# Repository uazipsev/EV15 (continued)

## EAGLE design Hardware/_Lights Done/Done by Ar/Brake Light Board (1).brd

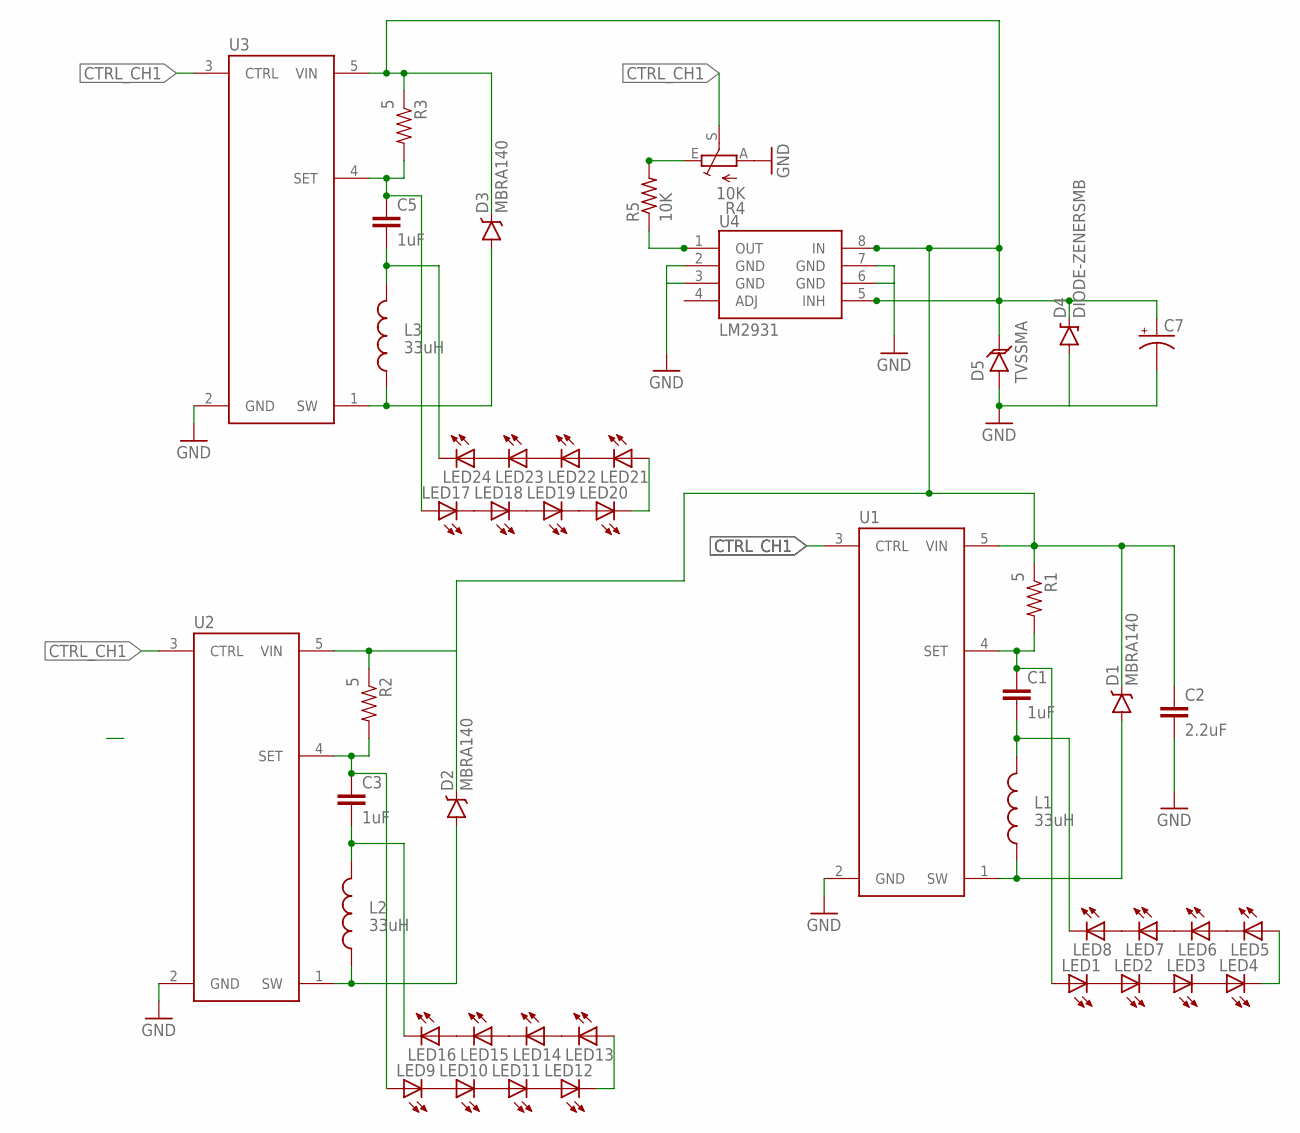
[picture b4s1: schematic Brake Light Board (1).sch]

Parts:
C1, C3, C5: 1uF; 1206
C2: 2.2uF; 1206
C7: CAP_POL6032; EIA6032
D1, D2, D3: MBRA140; SMA-DIODE
D4: DIODE-ZENERSMB; SMB-DIODE
D5: TVSSMA; SMA-DIODE
L1, L2, L3: 33uH; SRN6045
LED1, LED2, LED3, LED4, LED5, LED6, LED7, LED8, LED9, LED10, LED11, LED12, LED13, LED14, LED15, LED16, LED17, LED18, LED19, LED20, LED21, LED22, LED23, LED24: LED5MM
R1, R2, R3: 5; 0805
R4: 10K; B25P
R5: 10K; R0805
U1, U2, U3: AL8805; SOT23-5
U4: LM2931; SO08

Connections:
CTRL_CH1: R4.S, U1.3 (CTRL), U2.3 (CTRL), U3.3 (CTRL)
GND: C2.2, C7.P$2 (-), D4.A, D5.A, R4.A, U1.2 (GND), U2.2 (GND), U3.2 (GND), U4.2 (GND), U4.6 (GND), U4.7 (GND)
unnamed: LED1.K (C), LED2.A
unnamed: LED2.K (C), LED3.A
unnamed: LED3.K (C), LED4.A
unnamed: C1.2, L1.2, LED8.K (C)
unnamed: LED5.K (C), LED6.A
unnamed: LED6.K (C), LED7.A
unnamed: LED7.K (C), LED8.A
unnamed: LED9.K (C), LED10.A
unnamed: LED4.K (C), LED5.A
unnamed: LED10.K (C), LED11.A
unnamed: LED11.K (C), LED12.A
unnamed: C3.2, L2.2, LED16.K (C)
unnamed: LED13.K (C), LED14.A
unnamed: LED14.K (C), LED15.A
unnamed: LED15.K (C), LED16.A
unnamed: LED12.K (C), LED13.A
unnamed: LED17.K (C), LED18.A
unnamed: LED18.K (C), LED19.A
unnamed: LED19.K (C), LED20.A
unnamed: C5.2, L3.2, LED24.K (C)
unnamed: LED21.K (C), LED22.A
unnamed: LED22.K (C), LED23.A
unnamed: LED23.K (C), LED24.A
unnamed: LED20.K (C), LED21.A
unnamed: R4.E, R5.2
unnamed: R5.1, U4.1 (OUT)
OUT+: C1.1, LED1.A, R1.2, U1.4 (SET)
OUT+1: C3.1, LED9.A, R2.2, U2.4 (SET)
OUT+2: C5.1, LED17.A, R3.2, U3.4 (SET)
SW: D1.A, L1.1, U1.1 (SW)
SW1: D2.A, L2.1, U2.1 (SW)
SW2: D3.A, L3.1, U3.1 (SW)
VIN: C2.1, C7.P$1 (+), D1.C, D2.C, D3.C, D4.C, D5.C, R1.1, R2.1, R3.1, U1.5 (VIN), U2.5 (VIN), U3.5 (VIN), U4.5 (INH), U4.8 (IN)

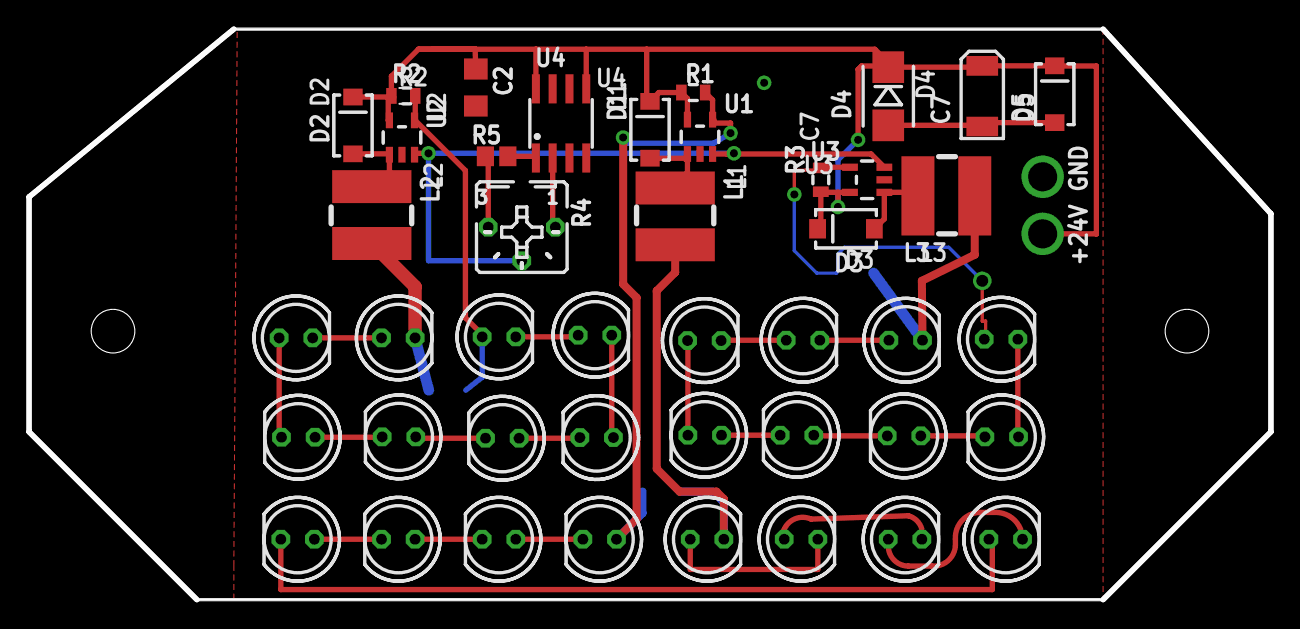
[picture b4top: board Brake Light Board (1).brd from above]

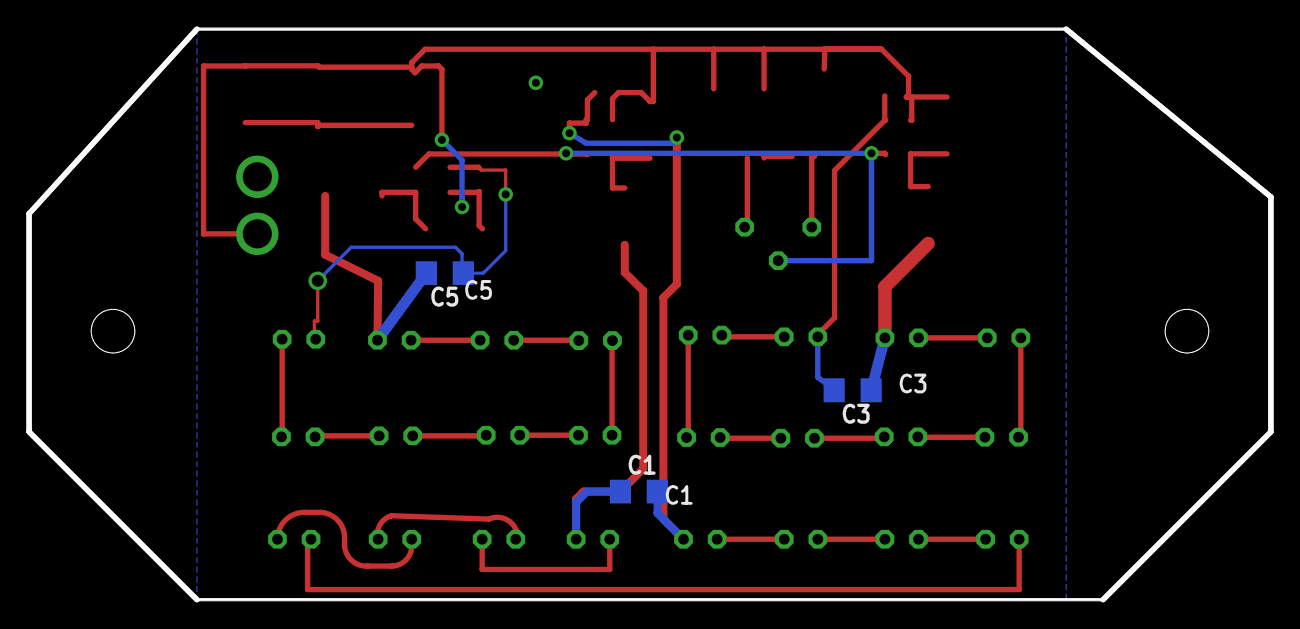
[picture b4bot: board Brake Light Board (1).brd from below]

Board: 2 copper layers, 94.0 x 43.2 mm, 46 parts (3 on the bottom side), 35 nets.

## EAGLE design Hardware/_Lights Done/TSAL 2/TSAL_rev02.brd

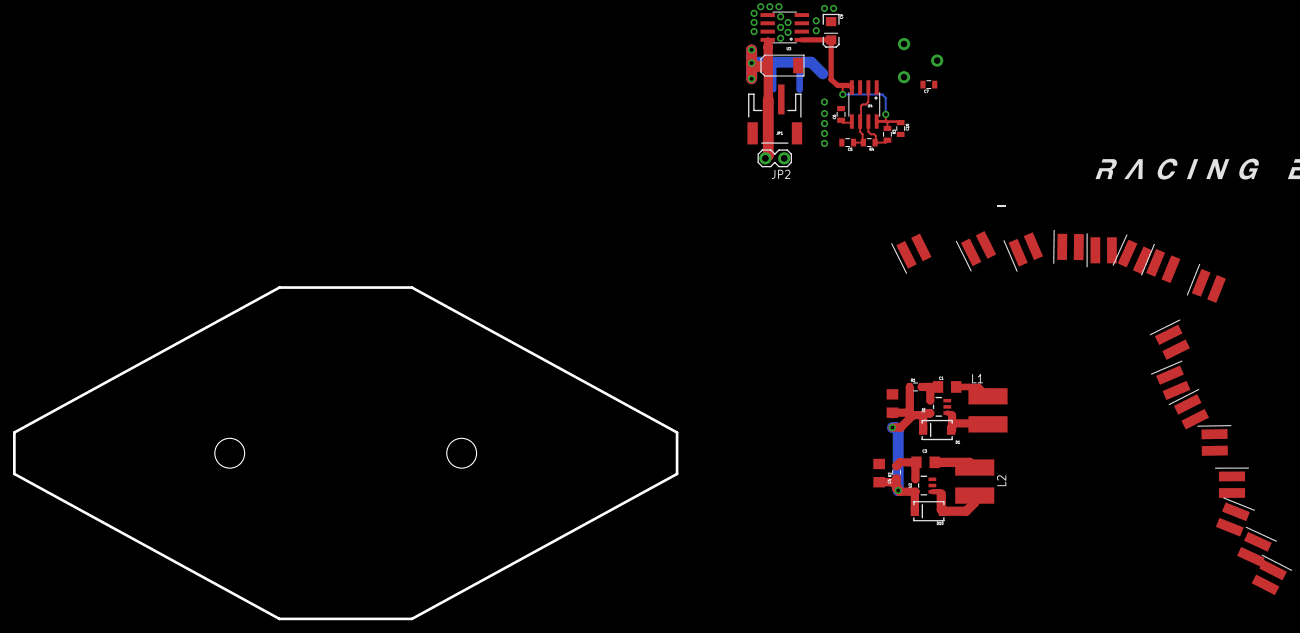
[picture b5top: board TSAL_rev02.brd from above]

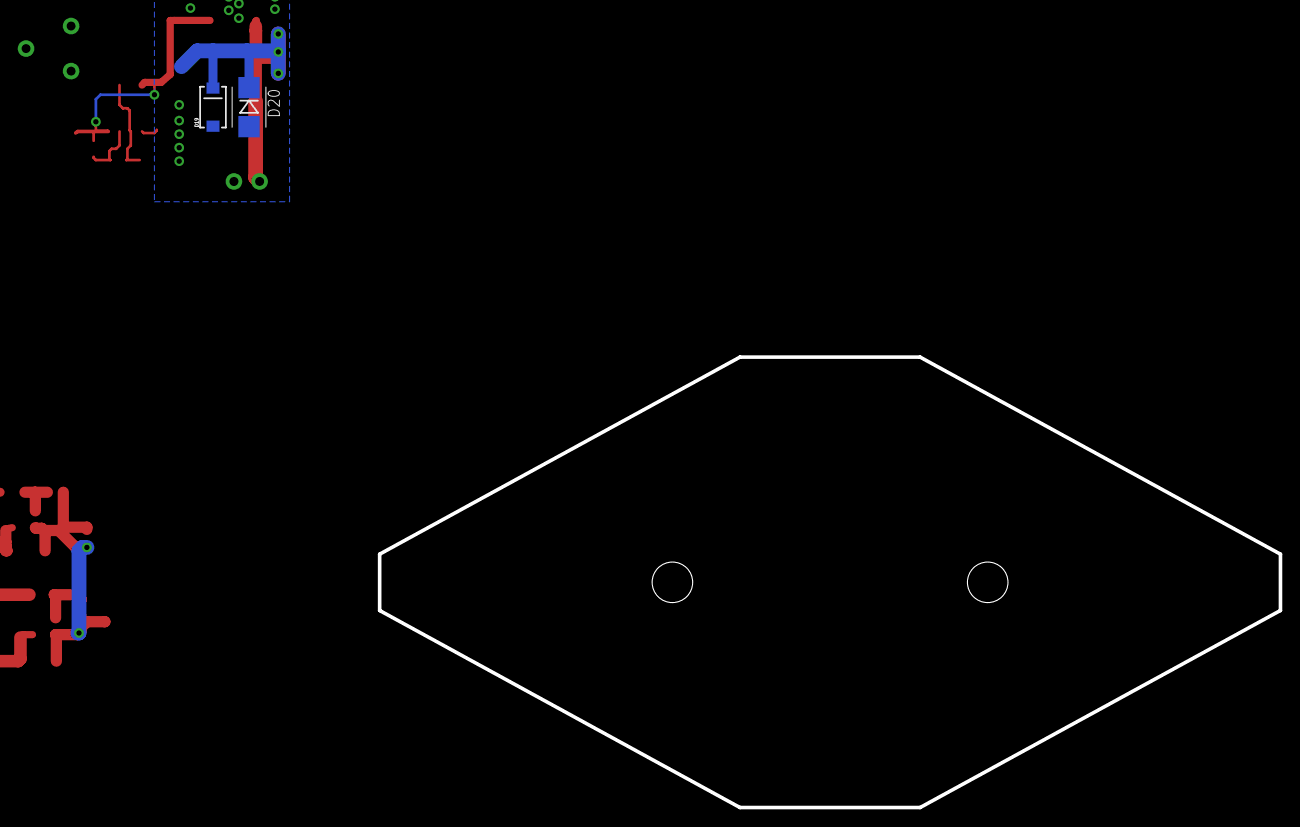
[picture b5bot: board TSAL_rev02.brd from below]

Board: 2 copper layers, 101.6 x 50.8 mm, 44 parts (2 on the bottom side), 28 nets.

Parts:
C1, C3: 1uF; 1206
C2, C4: 2.2uF; 1206
C5: 47uF; 0805
C6, C7: 10uF; 0805
C8: EIA6032
C9: EIA3216
C10: .1uF; 0805
D1, D10: MBRA140; SMA-DIODE
D2, D3, D4, D5, D6, D7, D8, D9, D11, D12, D13, D14, D15, D16, D17, D18: LED-SM
D19: TVS; SMA-DIODE
D20: 30v; SMB-DIODE
JP1: M02-JST-2MM-SMT; JST-2-SMD
JP2: M02LOCK; 1X02_LOCK
L1, L2: 33uH; SRN6045
R1, R2: 5R; 0805
R3: 10k; 0805
R4: 1k; 0805
RV1: TRIM_POT
U1, U2: SOT23-5
U3: LM2931D-5.0R2G; SO08
U4: SO08
U$1: LOGOL; L-L

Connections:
+5V: C9.A, C10.1, R3.1, U3.1, U4.4, U4.8
GND: C2.2, C4.2, C5.2, C6.2, C7.2, C8.P$2, C9.C, C10.2, D19.A, D20.A, JP1.1, JP2.1, RV1.3, U1.2, U2.2, U3.2, U3.3, U3.5, U3.6, U3.7, U4.1
unnamed: D2.C, D3.A
unnamed: D4.C, D5.A
unnamed: D6.C, D7.A
unnamed: D8.C, D9.A
unnamed: D3.C, D4.A
unnamed: D5.C, D6.A
unnamed: D7.C, D8.A
unnamed: D11.C, D12.A
unnamed: D13.C, D14.A
unnamed: D15.C, D16.A
unnamed: D17.C, D18.A
unnamed: D12.C, D13.A
unnamed: D14.C, D15.A
unnamed: D16.C, D17.A
unnamed: R3.2, R4.1, U4.7
unnamed: C5.1, R4.2, U4.2, U4.6
unnamed: C6.1, U4.5
unnamed: RV1.2, U4.3
unnamed: C7.1, RV1.1, U1.3, U2.3
OUT+: C1.1, D2.A, R1.2, U1.4
OUT+1: C3.1, D11.A, R2.2, U2.4
OUT-: C1.2, D9.C, L1.2
OUT-1: C3.2, D18.C, L2.2
SW: D1.A, L1.1, U1.1
SW1: D10.A, L2.1, U2.1
VIN: C2.1, C4.1, C8.P$1, D1.C, D10.C, D19.C, D20.C, JP1.2, JP2.2, R1.1, R2.1, U1.5, U2.5, U3.8

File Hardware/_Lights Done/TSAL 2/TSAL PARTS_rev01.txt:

Partlist

Exported from TSAL_rev01.sch at 1/11/15 2:55 PM

EAGLE Version 6.5.0 Copyright (c) 1988-2013 CadSoft

Assembly variant: 

Part     Value           Device                 Package   Library                    Sheet

C1       1uF             1.0UF50V10%(1206)      1206      SparkFun-Capacitors        1
C2       2.2uF           2.2UF50V10%(1206)      1206      SparkFun-Capacitors        1
C3       1uF             1.0UF50V10%(1206)      1206      SparkFun-Capacitors        1
C4       2.2uF           2.2UF50V10%(1206)      1206      SparkFun-Capacitors        1
C5       47uF            CAP0805                0805      SparkFun-Capacitors        1
C6       10uF            CAP0805                0805      SparkFun-Capacitors        1
C7       10uF            CAP0805                0805      SparkFun-Capacitors        1
C8                       CAP_POL6032            EIA6032   SparkFun-Capacitors        1
C9                       CAP_POL1206            EIA3216   SparkFun-Capacitors        1
C10      .1uF            CAP0805                0805      SparkFun-Capacitors        1
D1       MBRA140         DIODE-SCHOTTKY-MBRA140 SMA-DIODE SparkFun-DiscreteSemi      1
D2                       LED                    LED-SM    FSAE Eletric               1
D3                       LED                    LED-SM    FSAE Eletric               1
D4                       LED                    LED-SM    FSAE Eletric               1
D5                       LED                    LED-SM    FSAE Eletric               1
D6                       LED                    LED-SM    FSAE Eletric               1
D7                       LED                    LED-SM    FSAE Eletric               1
D8                       LED                    LED-SM    FSAE Eletric               1
D9                       LED                    LED-SM    FSAE Eletric               1
D10      MBRA140         DIODE-SCHOTTKY-MBRA140 SMA-DIODE SparkFun-DiscreteSemi      1
D11                      LED                    LED-SM    FSAE Eletric               1
D12                      LED                    LED-SM    FSAE Eletric               1
D13                      LED                    LED-SM    FSAE Eletric               1
D14                      LED                    LED-SM    FSAE Eletric               1
D15                      LED                    LED-SM    FSAE Eletric               1
D16                      LED                    LED-SM    FSAE Eletric               1
D17                      LED                    LED-SM    FSAE Eletric               1
D18                      LED                    LED-SM    FSAE Eletric               1
D19      TVS             TVS                    SMA-DIODE SparkFun-DiscreteSemi      1
D20      30v             DIODE-ZENERSMB         SMB-DIODE SparkFun-DiscreteSemi      1
JP1      M02-JST-2MM-SMT M02-JST-2MM-SMT        JST-2-SMD SparkFun-Connectors        1
JP2      M02LOCK         M02LOCK                1X02_LOCK SparkFun-Connectors        1
L1       33uH            INDUCTORBOURNS_SRN6045 SRN6045   SparkFun-Passives          1
L2       33uH            INDUCTORBOURNS_SRN6045 SRN6045   SparkFun-Passives          1
R1       5R              0.3OHM-1/8W-1%(0805)   0805      SparkFun-Resistors         1
R2       5R              0.3OHM-1/8W-1%(0805)   0805      SparkFun-Resistors         1
R3       10k             0.3OHM-1/8W-1%(0805)   0805      SparkFun-Resistors         1
R4       1k              0.3OHM-1/8W-1%(0805)   0805      SparkFun-Resistors         1
RV1                      POTTRIM                TRIM_POT  SparkFun-Electromechanical 1
U1                       AL8805                 SOT23-5   SparkFun-PowerIC           1
U2                       AL8805                 SOT23-5   SparkFun-PowerIC           1
U3       LM2931D-5.0R2G  LM2931                 SO08      SparkFun-PowerIC           1
U4                       NE555D                 SO08      SparkFun-AnalogIC          1

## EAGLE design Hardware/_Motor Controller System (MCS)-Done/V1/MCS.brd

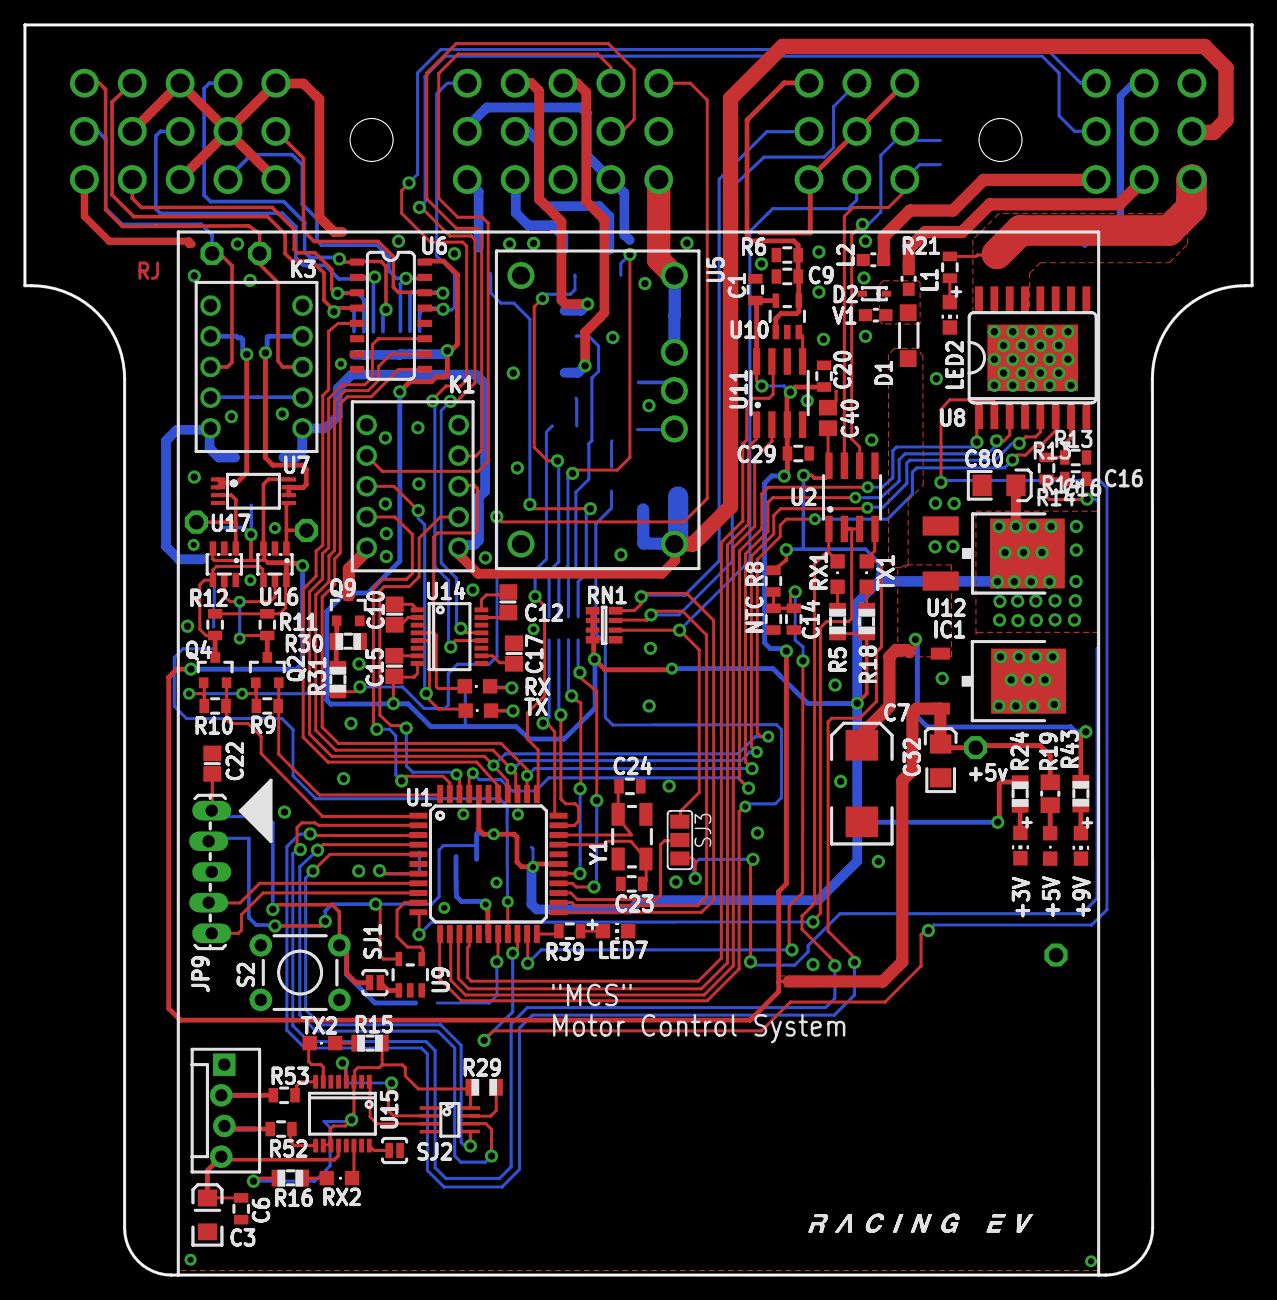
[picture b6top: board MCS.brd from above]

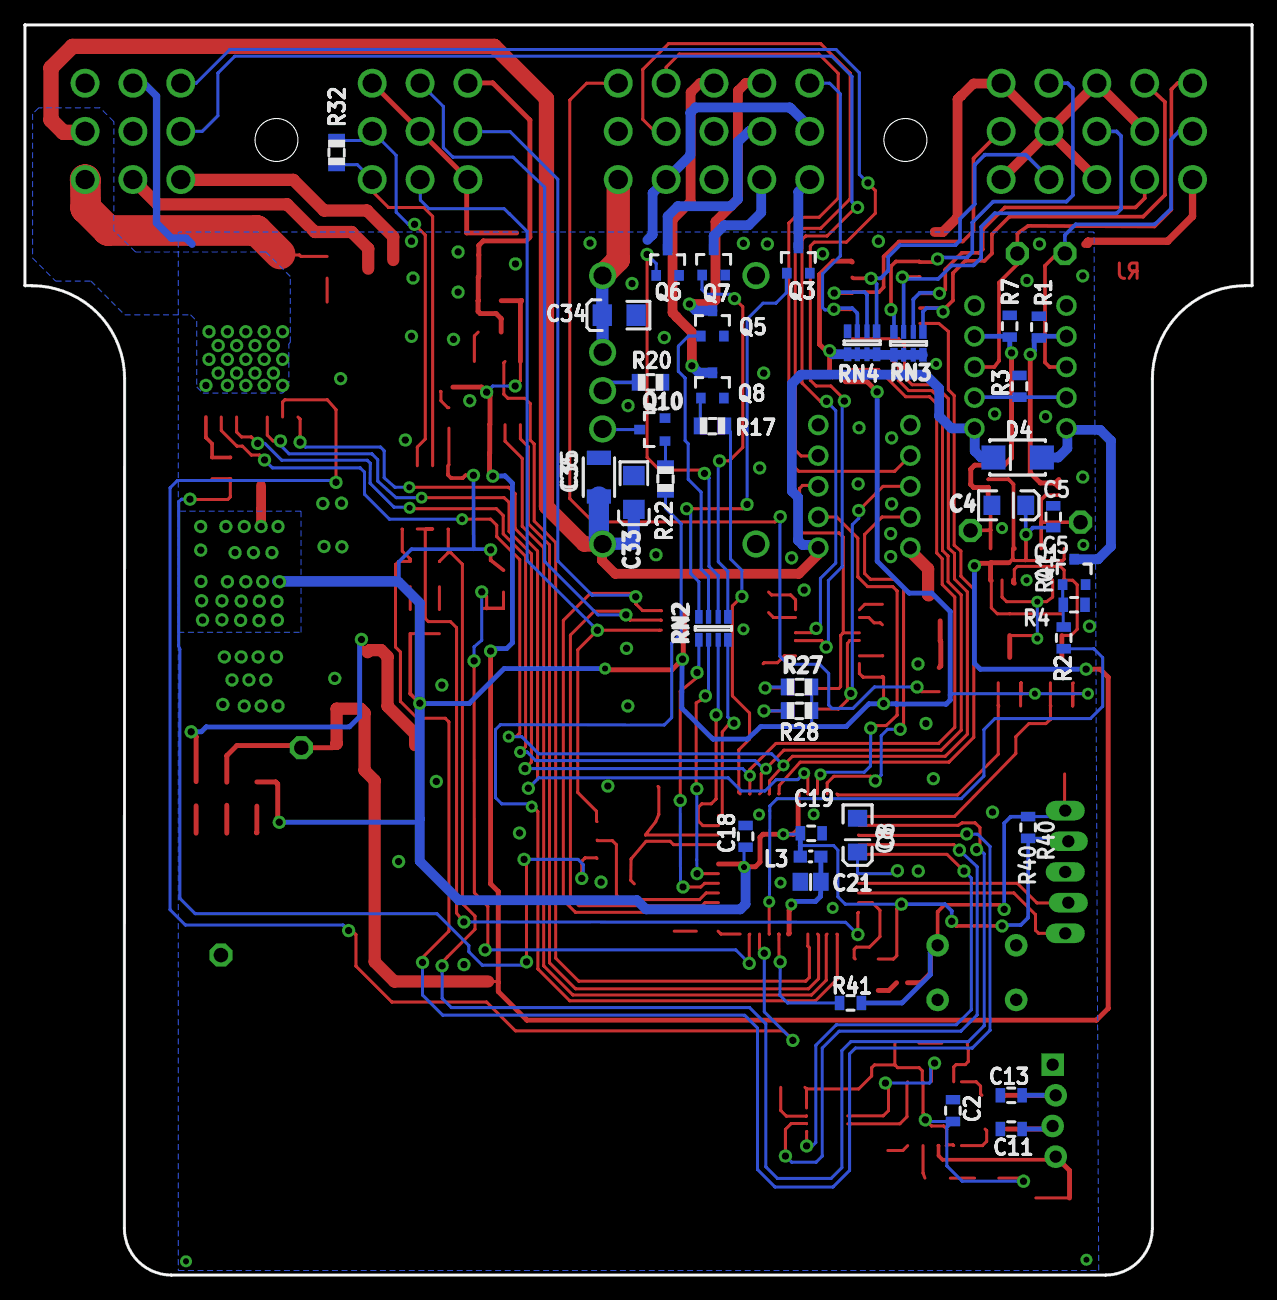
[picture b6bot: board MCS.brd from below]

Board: 2 copper layers, 101.6 x 103.5 mm, 133 parts (37 on the bottom side), 126 nets.

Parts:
+3V, +9V: CHIP-LED0805
+5V: Green; CHIPLED_0805
C1, C5, C14, C18, C19, C20, C29: 0.1uF; 0805
C2, C6: 0.1uf; 0805
C3: 4.7uF; EIA3216
C4, C8: 10uF; EIA3216
C7: 100uF; EIA7343
C9, C16: 10pF; 0805
C10, C12, C15, C17, C40: .1uF; C0805
C11, C13: 47pf; 0805
C21: 100n; C0805
C22: 10n; C0805
C23, C24: 12pF; 0805
C32, C33, C34, C80: 10uF; POLC1206
C35: 1uf; 1210
CASE2: 581-01-48-009
D1: 1N4001; SOD123
D2: MM5Z30; SOD-523F
D4: SMA-DIODE_ALT
IC1: 7805DT; TO252
JP9: ICSP; 1X05_LOCK_LONGPADS
JP13: MOLEX-1X4_LOCK
K1, K3: TQ2-2M-24V
L1, L2, L3: FB; 0603
LED2, LED7: CHIP-LED0805
NTC: 0805
Q1, Q2, Q3, Q4, Q5, Q6, Q7, Q8, Q9, Q10: BSS123; SOT23-3
R1, R6, R7, R8, R11, R12, R13, R14, R40: 10k; 0805
R2: 1k; 0805
R3: 100; 0805
R4: 100k; 0805
R5, R15, R17, R22, R27, R29, R31: 1K; R0805
R9, R10: 2k; 0805
R16, R18, R28: 1k; R0805
R19: 1K; M0805
R20: 383k; R0805
R21: 3.3k; 0805
R24: 499; R0805
R30: 10K; R0805
R32: 120; R0805
R39, R41: 499; 0805
R43: 1.2k; R0805
R52, R53: 27; 0805
RN1, RN2, RN3, RN4: RN-4; CRA06S
RX, RX2: CHIPLED_0805
RX1: RED; CHIPLED_0805
S2: ts; TACTILE-PTH
SJ1: SJ-NO; SJ_2S-NO
SJ2: PAD-JUMPER-2-NO_YES_SILK
SJ3: PAD-JUMPER-3-NO_YES_SILK_FULL_BOX
TP1, TP2, TP3, TP4, TP5, TP8: TESTPOINT; 4952
TX, TX2: CHIPLED_0805
TX1: GREEN; CHIPLED_0805
U1: DSPIC33FJ128GP804; TQFP-44
U2: SN75HVD08DR; SO-8
U4: SN74LVC2G241DCTR; VFSOP-8
U5: PTN78060HAH
U6: SN74HC251_SMD; SO016
U7: LM158; TSSOP-08
U8: VND7040AJTR-E; SO-16-POWER
U9: MAX823; SOT23-5L
U10: OPA344; SOT23-5
U11: X9015_DIGI_POTS; SO08
U12: NCP1117DT33T5G; V-REG_DPACK
U14: ADM3101E; SSOP-16
U15: FT230X; SSOP-16
U16, U17: MCP4725; SOT23-6
U$1: LOGOM; L-M
U$2: INDPK1; PICKIT-PIN-1
V1: 13Vdc; 0603
Y1: 12Mhz; CRYSTAL-SMD-5X3

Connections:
3V: C2.1, R15.2, R16.2, R29.2, U4.8, U15.3, U15.10, U15.11
12V-EN: R22.1, U1.12
!CS: U1.15, U11.7
!RST: U1.20, U8.2
+: CASE2.45, L1.1
+3V3: C15.2, C18.1, C19.1, C40.1, C80.1, JP9.2, L3.2, Q2.1, Q4.1, R5.2, R8.2, R9.2, R10.2, R18.2, R24.2, R27.2, R28.2, R40.2, RN1.1, RN1.2, RN1.3, RN1.4, RN3.5, RN3.6, RN3.7, RN3.8, RN4.6, RN4.7, RN4.8, U1.28, U1.40, U2.8, U6.16, U9.5, U12.4, U14.8
+5V: C1.1, C4.A, C5.1, C20.1, C29.1, C32.1, IC1.2, R11.2, R12.2, R19.1, TP2.P$1, U7.8, U10.5, U11.3, U11.8, U16.3, U16.6, U17.3
+9V: C7.A, D1.C, IC1.1, R43.2, U12.3
+12V: C34.1, CASE2.30, U5.5, U5.6
+24V: C33.1, C35.1, CASE2.47, D4.C, K1.1, K3.1, U5.2, U8.EP
-: CASE2.42, L2.1
A: U1.37, U6.11, U8.6
ASEN: C16.1, R14.2, SJ3.3
B: U1.36, U6.10, U8.5
BOX_TEMP: C14.1, NTC.2, R8.1, U1.21
C: U1.35, U6.9, U8.3
DAC-EN: R2.2, U1.19
FAN: CASE2.48, R21.2, U8.13, U8.14, U8.15, U8.16
FAN-PWM: U1.41, U8.1
GND: +3V.C, +5V.C, +9V.C, C1.2, C2.2, C3.C, C4.C, C5.2, C6.2, C7.C, C8.C, C9.2, C11.2, C13.2, C14.2, C16.2, C17.1, C18.2, C19.2, C20.2, C21.2, C22.2, C23.2, C24.2, C29.2, C32.2, C33.2, C34.2, C35.2, C40.2, C80.2, CASE2.3, CASE2.5, CASE2.7, CASE2.9, CASE2.11, CASE2.13, CASE2.15, CASE2.17, CASE2.27, CASE2.33, CASE2.35, CASE2.37, CASE2.43, D2.A, IC1.3, JP9.3, JP13.1, L2.2, LED2.C, LED7.C, NTC.1, Q1.2, Q3.2, Q5.2, Q6.2, Q7.2, Q8.2, Q9.2, Q10.2, R1.2, R3.2, R4.1, R6.1, R7.2, R13.1, R20.1, R30.2, S2.1, SJ2.1, TP1.P$1, U1.6, U1.16, U1.29, U1.39, U2.5, U4.1, U4.4, U5.1, U5.7, U6.7, U6.8, U7.4, U8.4, U9.2, U10.2, U11.4, U11.6, U12.1, U14.9, U15.5, U15.13, U16.2, U17.2, U17.6, V1.1
INC: U1.14, U11.1
MC1-B: RN2.3, U1.32
MC1-F: RN2.1, U1.26
MC1-PE: RN2.4, U1.33
MC1-R: RN2.2, U1.27
MC1-RE: R17.1, U1.34
MC-1-B: CASE2.2, K3.8, TP4.P$1
MC-1-T: CASE2.1, K3.3, TP5.P$1
MC-PG-EN: CASE2.28, R31.1
MCRX: K1.3, RX.C, U14.4
MCTX: K1.8, TX.C, U14.5
unnamed: C22.1, JP9.1, R40.1, R41.1, S2.3, SJ1.2
unnamed: C21.1, L3.1, U1.17
unnamed: K3.7, R1.1, U7.1, U7.2
unnamed: C8.A, U1.7
unnamed: R39.2, U1.22
unnamed: +9V.A, R43.1
unnamed: Q3.1, RN2.8
unnamed: R41.2, U1.18
unnamed: CASE2.18, Q3.3
unnamed: SJ1.1, U9.1
unnamed: R15.1, TX2.A
unnamed: JP9.4, U1.8
unnamed: TX2.C, U15.7
unnamed: RX2.C, U15.14
unnamed: JP9.5, U1.9
unnamed: R16.1, RX2.A
unnamed: TP3.P$1, U7.5, U16.1
unnamed: K3.4, R7.1, U7.6, U7.7
unnamed: U4.2, U15.4
unnamed: Q5.1, RN2.7
unnamed: K3.2, K3.9, R3.1
unnamed: TP8.P$1, U7.3, U17.1
unnamed: LED2.A, R21.1
unnamed: U10.3, U11.5
unnamed: +3V.A, R24.1
unnamed: CASE2.19, Q5.3
unnamed: U4.3, U15.1
unnamed: R52.2, U15.9
unnamed: Q6.1, RN2.6
unnamed: CASE2.20, Q6.3
unnamed: R18.1, TX1.A
unnamed: R5.1, RX1.A
unnamed: SJ3.2, U1.25
unnamed: Q8.1, R17.2
unnamed: LED7.A, R39.1
unnamed: C24.1, U1.31, Y1.3
unnamed: C23.1, U1.30, Y1.1
unnamed: +5V.A, R19.2
unnamed: Q1.1, R2.1, R4.2
unnamed: D4.A, K3.10, Q1.3
unnamed: R13.2, R14.1, U8.7
unnamed: R53.2, U15.8
unnamed: C11.1, JP13.3, R52.1
unnamed: C10.1, U14.1
unnamed: C13.1, JP13.2, R53.1
unnamed: SJ2.2, U15.16
unnamed: D1.A, D2.C, L1.2, V1.2
unnamed: C10.2, U14.2
unnamed: C12.1, U14.16
unnamed: C12.2, U14.15
unnamed: C15.1, U14.7
unnamed: R29.1, U4.7
unnamed: CASE2.21, Q7.3
unnamed: CASE2.22, Q8.3
unnamed: C17.2, U14.10
unnamed: CASE2.40, U14.12
unnamed: CASE2.41, U14.13
unnamed: R27.1, RX.A
unnamed: R28.1, TX.A
unnamed: K1.10, Q9.3
unnamed: Q9.1, R30.1, R31.2
unnamed: R20.2, U5.4
unnamed: Q10.3, U5.3
unnamed: Q7.1, RN2.5
unnamed: Q10.1, R22.2
unnamed: C3.A, C6.1, JP13.4, U15.12
OUT: U1.38, U6.5
OUT-RX: CASE2.26, K1.4
OUT-TX: CASE2.25, K1.7
PUMP_OUTPUT_CONTROL: C9.1, CASE2.31, R6.2, U10.1, U10.4
RS-A: CASE2.38, R32.1, U2.6
RS-B: CASE2.39, R32.2, U2.7
RX2: K1.2, U1.42
RX3: U1.4, U4.6
RXD1: RX1.C, U1.2, U2.1
SCL: Q2.2, R9.1, U1.44
SCL_5V: Q2.3, R11.1, U16.5, U17.5
SDA: Q4.2, R10.1, U1.1
SDA_5V: Q4.3, R12.1, U16.4, U17.4
SP1: CASE2.4, RN3.1, U6.4
SP2: CASE2.6, RN3.2, U6.3
SP3: CASE2.8, RN3.3, U6.2
SP4: CASE2.10, RN3.4, U6.1
SP5: CASE2.12, RN4.1, U6.15
SP6: CASE2.14, RN4.2, U6.14
SP7: CASE2.16, RN4.3, U6.13
TEMP1: CASE2.32, RN1.8, U1.23
TEMP2: CASE2.34, RN1.7, U1.24
TEMP3: CASE2.36, RN1.6, SJ3.1
TX2: K1.9, U1.43
TX3: U1.5, U4.5
TXD1: TX1.C, U1.3, U2.4
U5-RE/DE: U1.11, U2.2, U2.3
UP/!DN: U1.13, U11.2
WDI: U1.10, U9.4
